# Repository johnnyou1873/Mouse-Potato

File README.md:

# Mouse-Potato
Micromouse design for AAMC 2024

## Major Components

### Microcontroller
STMicroelectronics STM32F411RETx

### Motors
*2x* CHF-GW12T-N20VA ABHL DC Worm Gear Motor
- Ratio: 42-A
- Voltage: 6V B45
- https://www.aliexpress.us/item/3256801422029348.html
- Requires shortening of the encoder board and resoldering of the cables

### Motor Driver
STMicroelectronics L293DD

### IMU
TDK InvenSense ICM-42688-P

### ToF Sensors
*3x* Adafruit VL6180X Time of Flight Micro-LIDAR Distance Sensor Breakout

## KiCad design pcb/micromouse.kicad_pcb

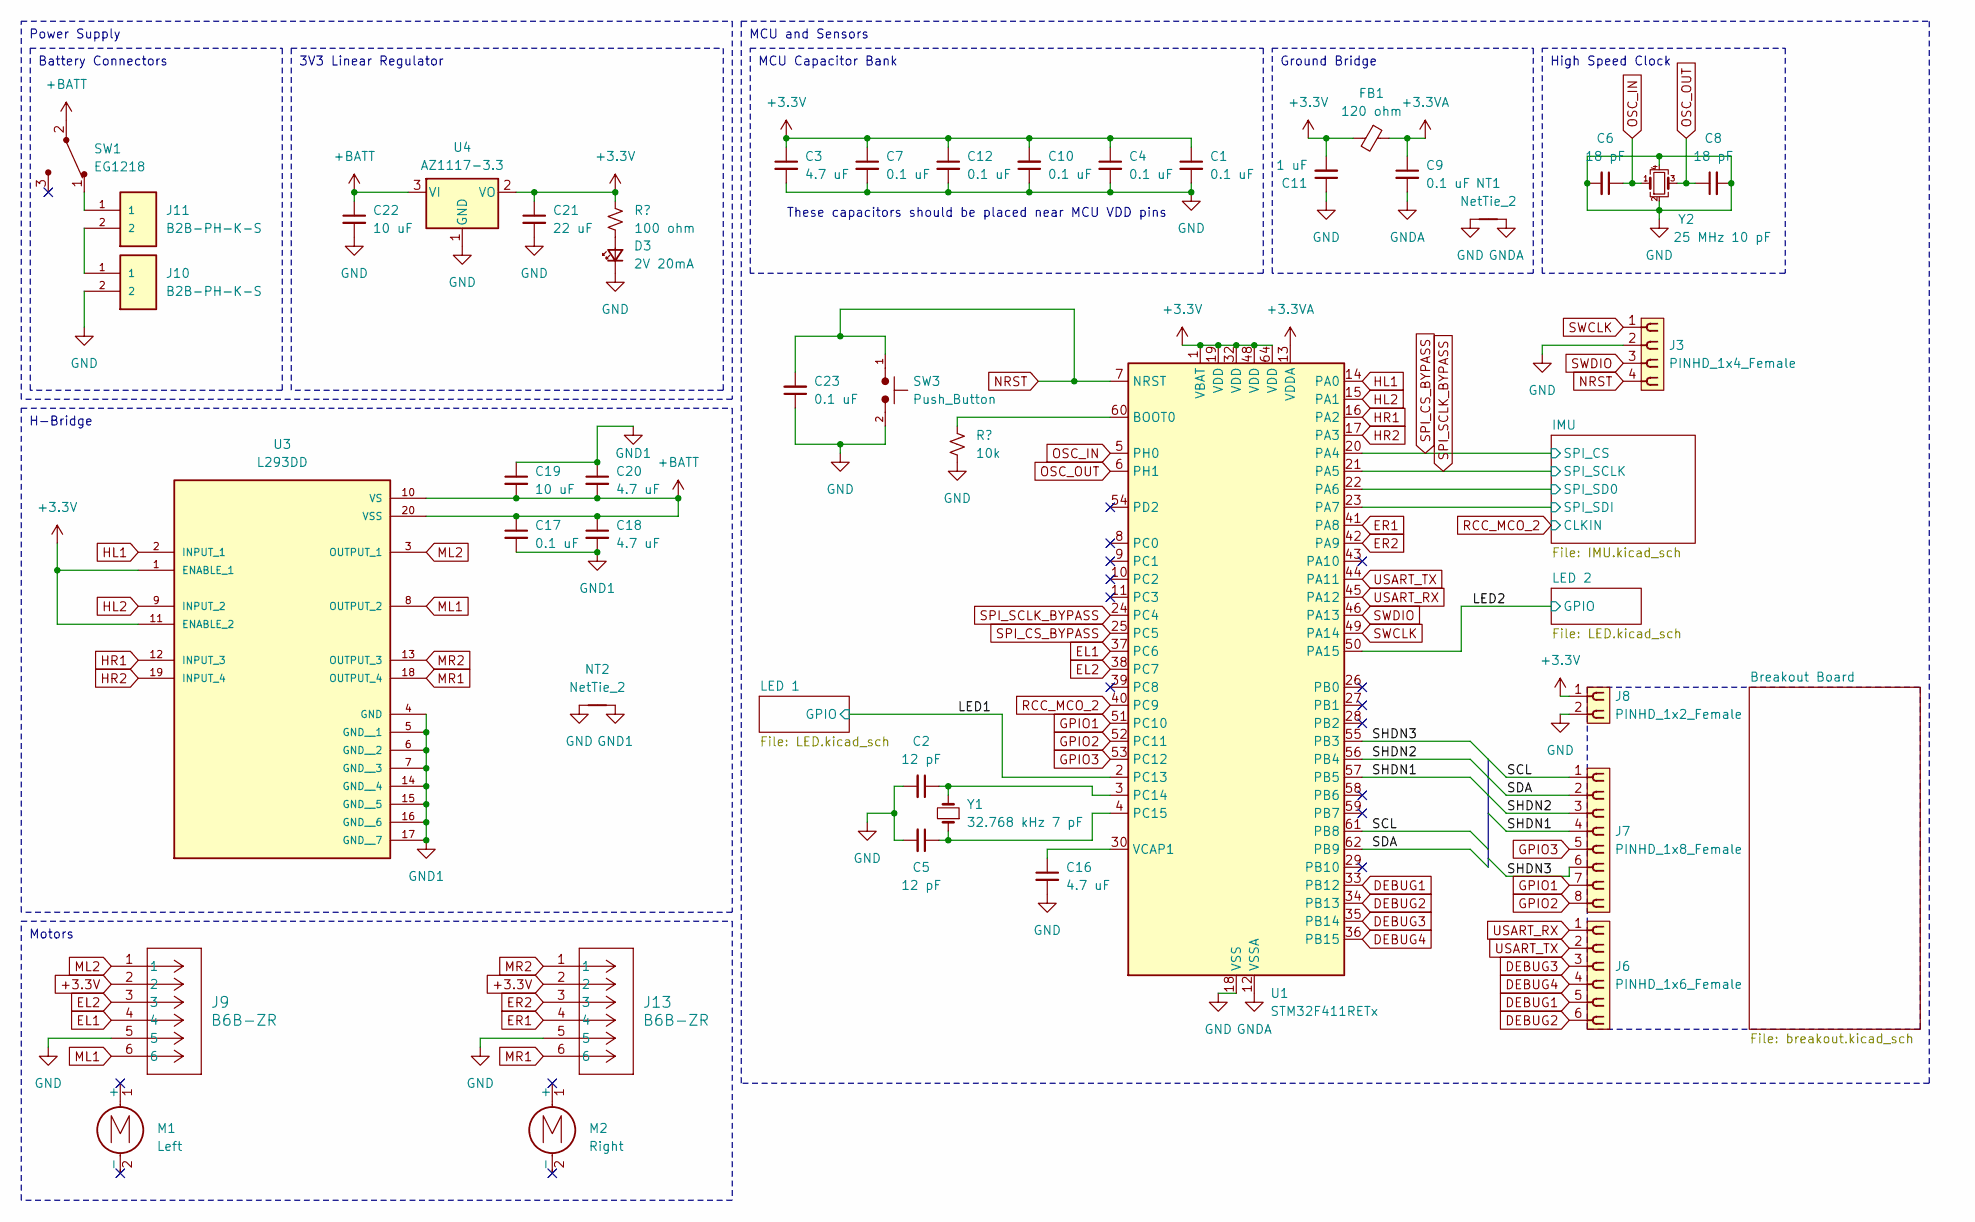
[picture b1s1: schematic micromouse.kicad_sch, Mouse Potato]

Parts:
C1, C4, C7, C9, C10, C12, C17, C23: 0.1 uF; C_0603_1608Metric
C2, C5: 12 pF; C_0603_1608Metric
C3, C16, C18, C20: 4.7 uF; C_0603_1608Metric
C6, C8: 18 pF; C_0603_1608Metric
C11: 1 uF; C_0603_1608Metric
C19, C22: 10 uF; C_0603_1608Metric
C21: 22 uF; C_0603_1608Metric
D3: 2V 20mA; LED_0603_1608Metric
FB1: 120 ohm; L_0603_1608Metric
J3: PINHD_1x4_Female; PinSocket_1x04_P2.54mm_Vertical
J6: PINHD_1x6_Female; PinSocket_2x03_P2.54mm_Vertical
J7: PINHD_1x8_Female; PinSocket_2x04_P2.54mm_Vertical
J8: PINHD_1x2_Female; PinSocket_1x02_P2.54mm_Vertical
J9, J13: B6B-ZR; CONN_B6B-ZR_JST
J10, J11: B2B-PH-K-S; JST_B2B-PH-K-S_LF__SN_; PARTREV N/A; DIGI-KEY_PART_NUMBER 455-1704-ND
M1: Left; MM_Motor_Left
M2: Right; MM_Motor_Right
NT1, NT2: NetTie_2; NetTie-2_SMD_Pad0.5mm
R2: 10k; R_0603_1608Metric
R5: 100 ohm; R_0603_1608Metric
SW1: EG1218; Switch_Slide_11.6x4mm_EG1218; MPN EG1218; Digi-Key_PN EG1903-ND
SW3: Push_Button; SolderJumper-2_P1.3mm_Open_Pad1.0x1.5mm
U1: STM32F411RETx; LQFP-64_10x10mm_P0.5mm
U3: L293DD; SOIC127P1032X265-20N; PARTREV N/A
U4: AZ1117-3.3; SOT-223-3_TabPin2
Y1: 32.768 kHz 7 pF; XTAL_SC32S-7PF20PPM_EPS
Y2: 25 MHz 10 pF; XTAL4P_RH100-25.000-10-F-3030-EXT-TR_RAL

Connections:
+3.3V: C1.1, C3.1, C4.1, C7.1, C10.2, C11.2, C12.1, C21.1, FB1.2, J8.1, J9.2, J13.2, R5.2, U1.1 (VBAT), U1.19 (VDD), U1.32 (VDD), U1.48 (VDD), U1.64 (VDD), U3.1 (ENABLE_1), U3.11 (ENABLE_2), U4.2 (VO); also elsewhere on the board
+3.3VA: C9.1, FB1.1, U1.13 (VDDA)
+BATT: C17.1, C18.1, C19.2, C20.2, C22.1, SW1.2, U3.10 (VS), U3.20 (VSS), U4.3 (VI)
/IMU/SPI_SD0: U1.22 (PA6); also elsewhere on the board
/IMU/SPI_SDI: U1.23 (PA7); also elsewhere on the board
/LED1: U1.2 (PC13); also elsewhere on the board
/LED2: U1.50 (PA15); also elsewhere on the board
/SCL: J7.1, U1.61 (PB8)
/SDA: J7.2, U1.62 (PB9)
/SHDN1: J7.4, U1.57 (PB5)
/SHDN2: J7.3, U1.56 (PB4)
/SHDN3: J7.6, U1.55 (PB3)
DEBUG1: J6.5, U1.33 (PB12)
DEBUG2: J6.6, U1.34 (PB13)
DEBUG3: J6.3, U1.35 (PB14)
DEBUG4: J6.4, U1.36 (PB15)
EL1: J9.4, U1.37 (PC6)
EL2: J9.3, U1.38 (PC7)
ER1: J13.4, U1.41 (PA8)
ER2: J13.3, U1.42 (PA9)
GND1: C17.2, C18.2, C19.1, C20.1, NT2.2, U3.4 (GND), U3.5 (GND__1), U3.6 (GND__2), U3.7 (GND__3), U3.14 (GND__4), U3.15 (GND__5), U3.16 (GND__6), U3.17 (GND__7)
GNDA: C9.2, NT1.2, U1.12 (VSSA)
GPIO1: J7.7, U1.51 (PC10)
GPIO2: J7.8, U1.52 (PC11)
GPIO3: J7.5, U1.53 (PC12)
HL1: U1.14 (PA0), U3.2 (INPUT_1)
HL2: U1.15 (PA1), U3.9 (INPUT_2)
HR1: U1.16 (PA2), U3.12 (INPUT_3)
HR2: U1.17 (PA3), U3.19 (INPUT_4)
ML1: J9.6, U3.8 (OUTPUT_2)
ML2: J9.1, U3.3 (OUTPUT_1)
MR1: J13.6, U3.18 (OUTPUT_4)
MR2: J13.1, U3.13 (OUTPUT_3)
NRST: C23.2, J3.4, SW3.1, U1.7 (NRST)
unnamed: D3.2 (A), R5.1
unnamed: J10.1, J11.2
unnamed: J11.1, SW1.1
unnamed: C2.1, U1.3 (PC14), Y1.2
unnamed: C5.1, U1.4 (PC15), Y1.1
unnamed: C16.1, U1.30 (VCAP1)
OSC_IN: C6.1, U1.5 (PH0), Y2.1
OSC_OUT: C8.1, U1.6 (PH1), Y2.3
RCC_MCO_2: U1.40 (PC9); also elsewhere on the board
SPI_CS_BYPASS: U1.20 (PA4), U1.25 (PC5); also elsewhere on the board
SPI_SCLK_BYPASS: U1.21 (PA5), U1.24 (PC4); also elsewhere on the board
SWCLK: J3.1, U1.49 (PA14)
SWDIO: J3.3, U1.46 (PA13)
USART_RX: J6.1, U1.45 (PA12)
USART_TX: J6.2, U1.44 (PA11)

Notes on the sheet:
H-Bridge
3V3 Linear Regulator
Ground Bridge
MCU and Sensors
Motors
MCU Capacitor Bank
Power Supply
High Speed Clock
Battery Connectors
These capacitors should be placed near MCU VDD pins

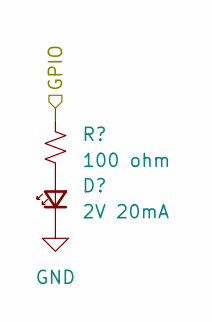
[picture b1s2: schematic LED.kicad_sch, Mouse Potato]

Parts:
D1: 2V 20mA; LED_0603_1608Metric
R1: 100 ohm; R_0603_1608Metric

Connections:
/LED1: R1.2; also elsewhere on the board
unnamed: D1.2 (A), R1.1

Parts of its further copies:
D2: 2V 20mA; LED_0603_1608Metric
R3: 100 ohm; R_0603_1608Metric

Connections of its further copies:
/LED2: R3.2; also elsewhere on the board
unnamed: D2.2 (A), R3.1

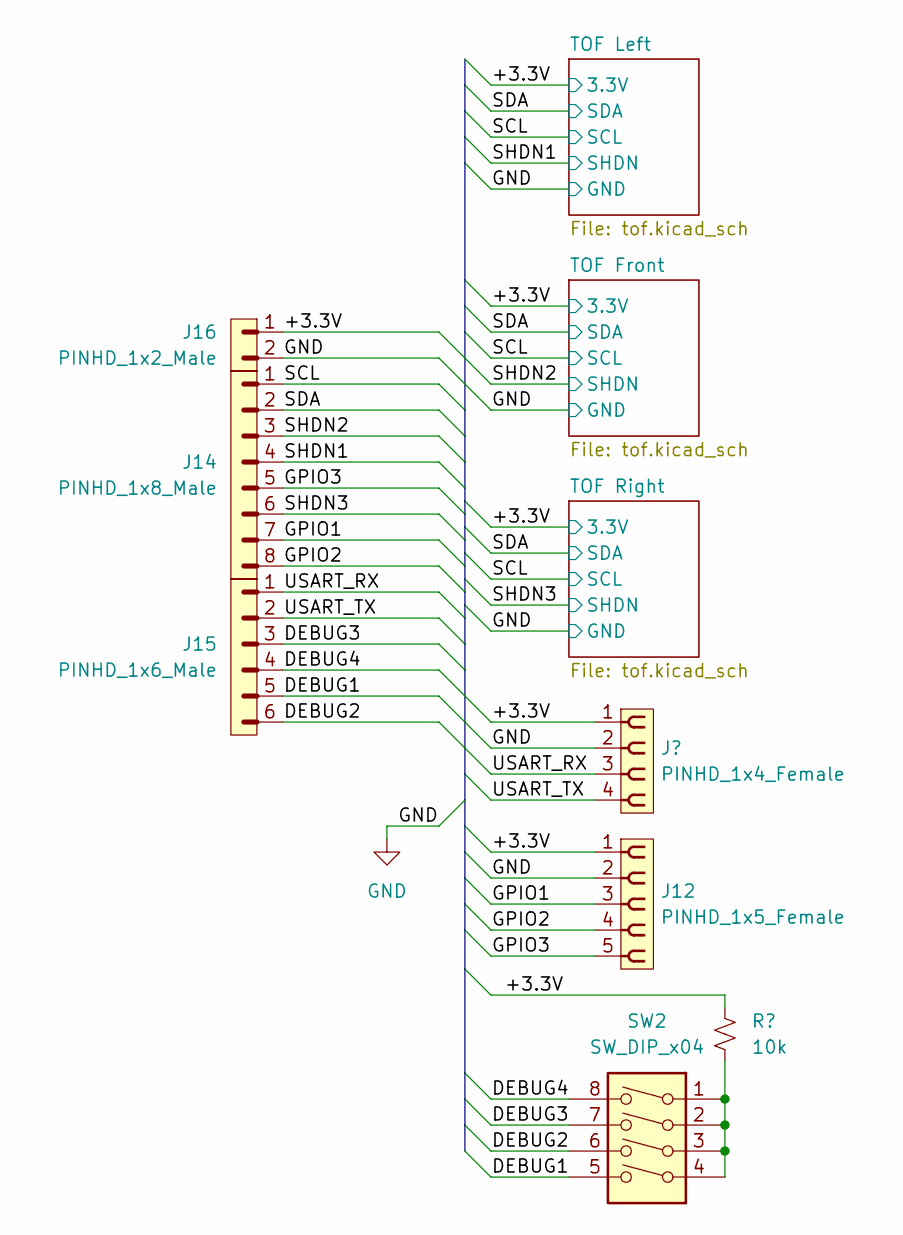
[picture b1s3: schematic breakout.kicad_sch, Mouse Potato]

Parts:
J5: PINHD_1x4_Female; PinSocket_1x04_P2.54mm_Vertical
J12: PINHD_1x5_Female; PinSocket_1x05_P2.54mm_Vertical
J14: PINHD_1x8_Male; PinHeader_2x04_P2.54mm_Vertical
J15: PINHD_1x6_Male; PinHeader_2x03_P2.54mm_Vertical
J16: PINHD_1x2_Male; PinHeader_1x02_P2.54mm_Vertical
R2: 10k; R_0603_1608Metric
SW2: SW_DIP_x04; 218-4LPST

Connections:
/Breakout Board/DEBUG1: J15.5, SW2.5
/Breakout Board/DEBUG2: J15.6, SW2.6
/Breakout Board/DEBUG3: J15.3, SW2.7
/Breakout Board/DEBUG4: J15.4, SW2.8
/Breakout Board/GPIO1: J12.3, J14.7
/Breakout Board/GPIO2: J12.4, J14.8
/Breakout Board/GPIO3: J12.5, J14.5
/Breakout Board/SCL: J14.1; also elsewhere on the board
/Breakout Board/SDA: J14.2; also elsewhere on the board
/Breakout Board/SHDN1: J14.4; also elsewhere on the board
/Breakout Board/SHDN2: J14.3; also elsewhere on the board
/Breakout Board/SHDN3: J14.6; also elsewhere on the board
/Breakout Board/USART_RX: J5.3, J15.1
/Breakout Board/USART_TX: J5.4, J15.2

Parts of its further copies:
R6: 10k; R_0603_1608Metric

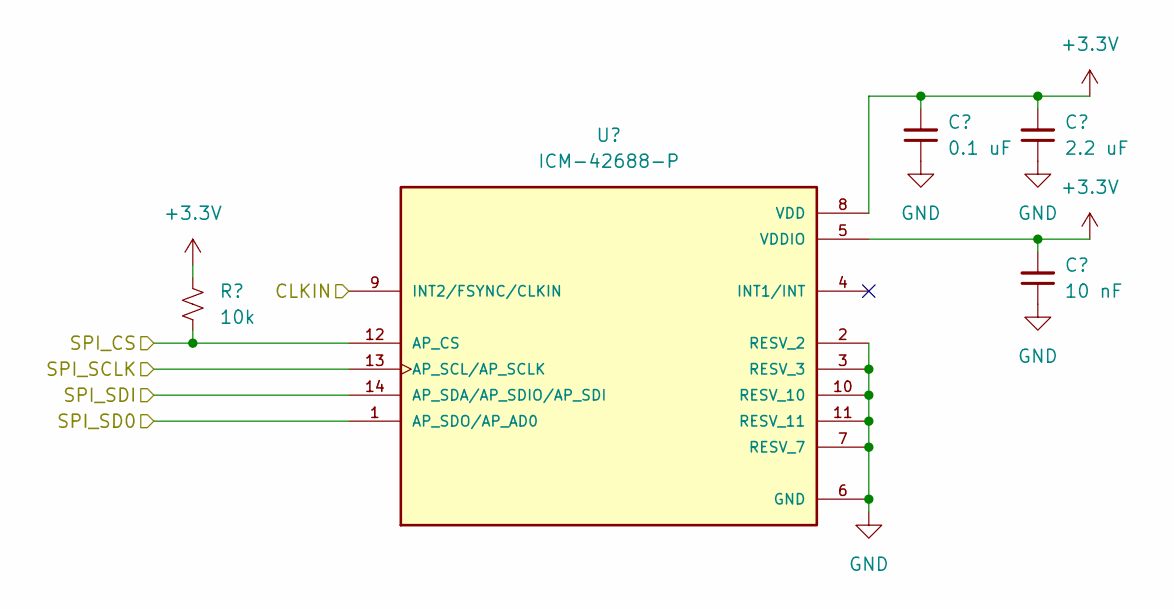
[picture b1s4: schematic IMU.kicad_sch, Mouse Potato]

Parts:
C13: 10 nF; C_0603_1608Metric
C14: 0.1 uF; C_0603_1608Metric
C15: 2.2 uF; C_0603_1608Metric
R4: 10k; R_0603_1608Metric
U2: ICM-42688-P; PQFN50P300X250X97-14N; PARTREV 1.2

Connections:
+3.3V: C13.2, C14.2, C15.2, R4.2, U2.5 (VDDIO), U2.8 (VDD); also elsewhere on the board
/IMU/SPI_SD0: U2.1 (AP_SDO/AP_AD0); also elsewhere on the board
/IMU/SPI_SDI: U2.14 (AP_SDA/AP_SDIO/AP_SDI); also elsewhere on the board
RCC_MCO_2: U2.9 (INT2/FSYNC/CLKIN); also elsewhere on the board
SPI_CS_BYPASS: R4.1, U2.12 (AP_CS); also elsewhere on the board
SPI_SCLK_BYPASS: U2.13 (AP_SCL/AP_SCLK); also elsewhere on the board

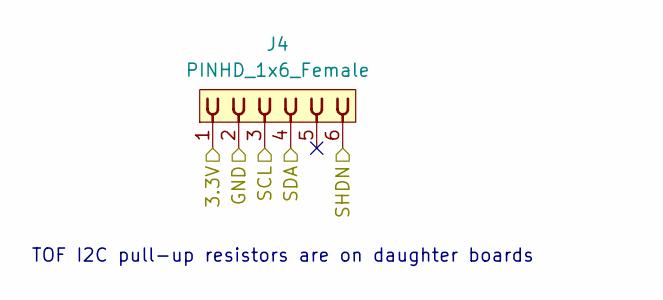
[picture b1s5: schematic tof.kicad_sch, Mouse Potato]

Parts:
J4: PINHD_1x6_Female; PinSocket_1x06_P2.54mm_Vertical

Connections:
/Breakout Board/SCL: J4.3; also elsewhere on the board
/Breakout Board/SDA: J4.4; also elsewhere on the board
/Breakout Board/SHDN3: J4.6; also elsewhere on the board

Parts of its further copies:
J1, J2: PINHD_1x6_Female; PinSocket_1x06_P2.54mm_Vertical

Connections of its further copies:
/Breakout Board/SCL: J1.3, J2.3; also elsewhere on the board
/Breakout Board/SDA: J1.4, J2.4; also elsewhere on the board
/Breakout Board/SHDN1: J1.6; also elsewhere on the board
/Breakout Board/SHDN2: J2.6; also elsewhere on the board

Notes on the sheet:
TOF I2C pull-up resistors are on daughter boards

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
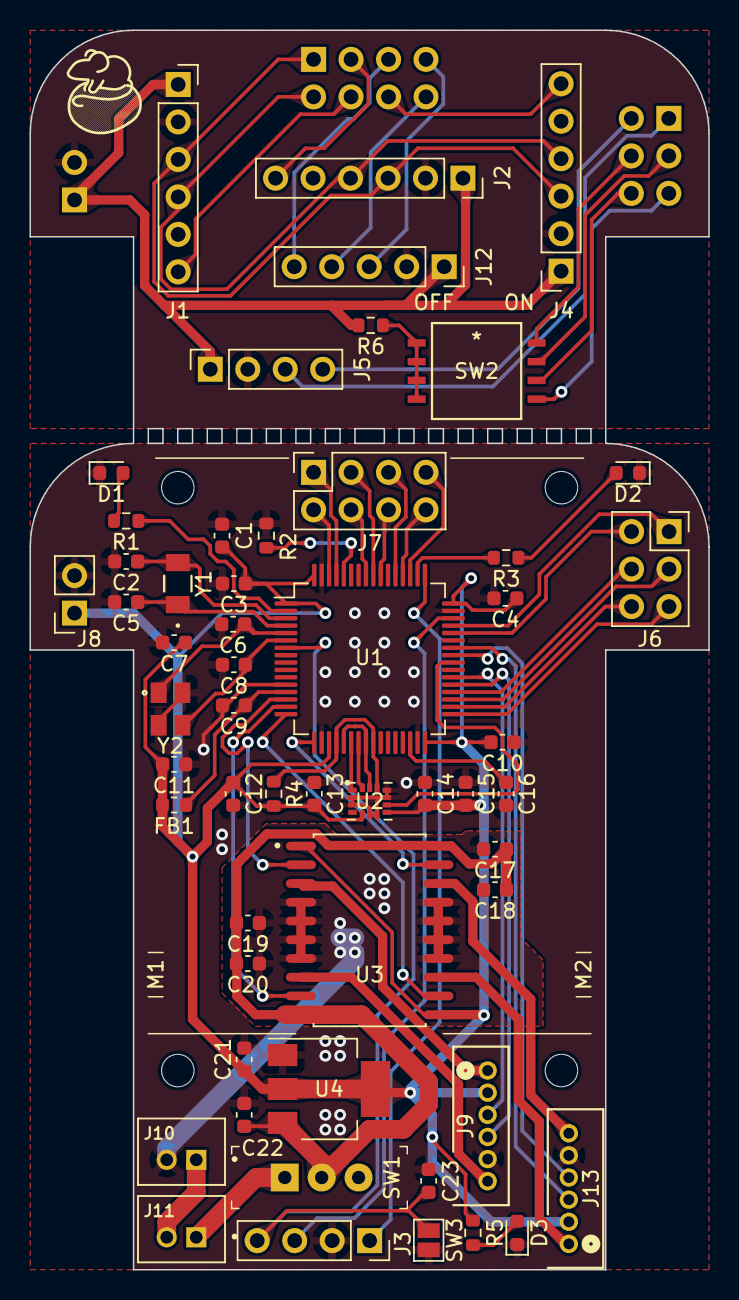
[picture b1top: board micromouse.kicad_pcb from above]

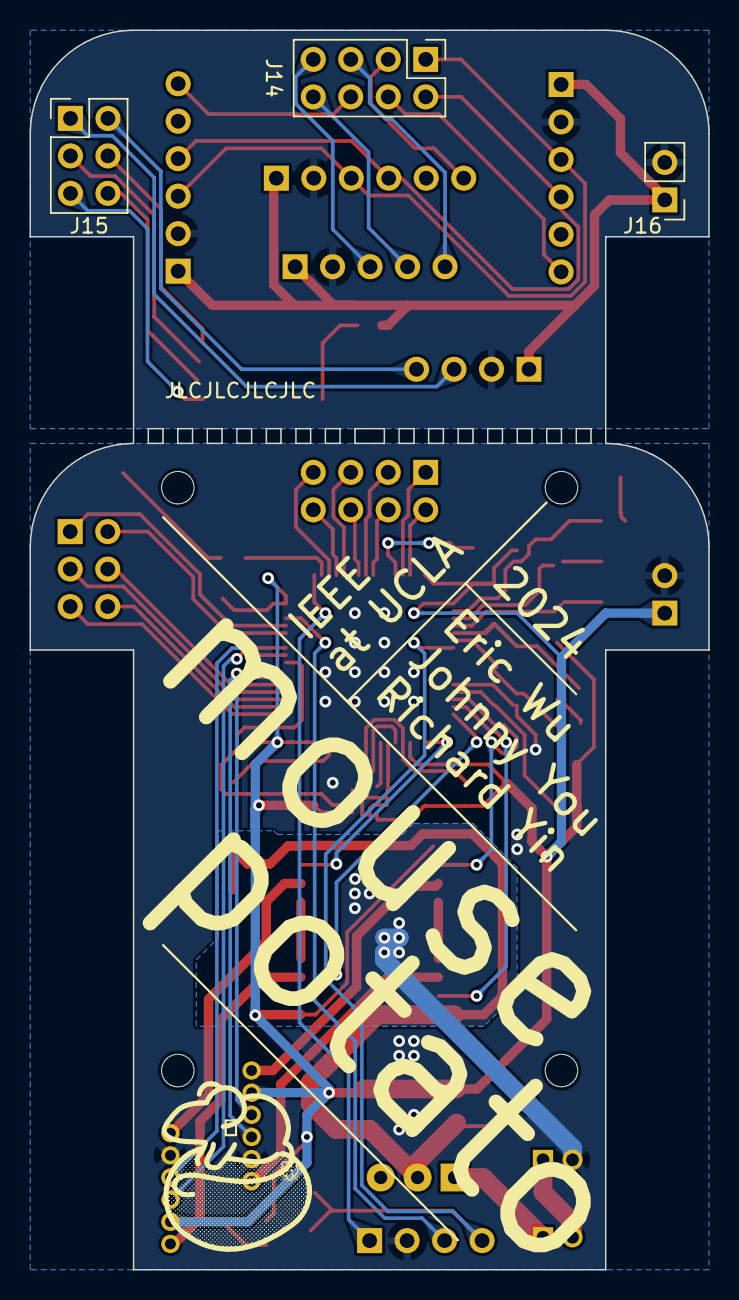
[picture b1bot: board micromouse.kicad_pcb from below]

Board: 2 copper layers, 46.0 x 84.0 mm, 62 parts (4 on the bottom side), 69 nets.

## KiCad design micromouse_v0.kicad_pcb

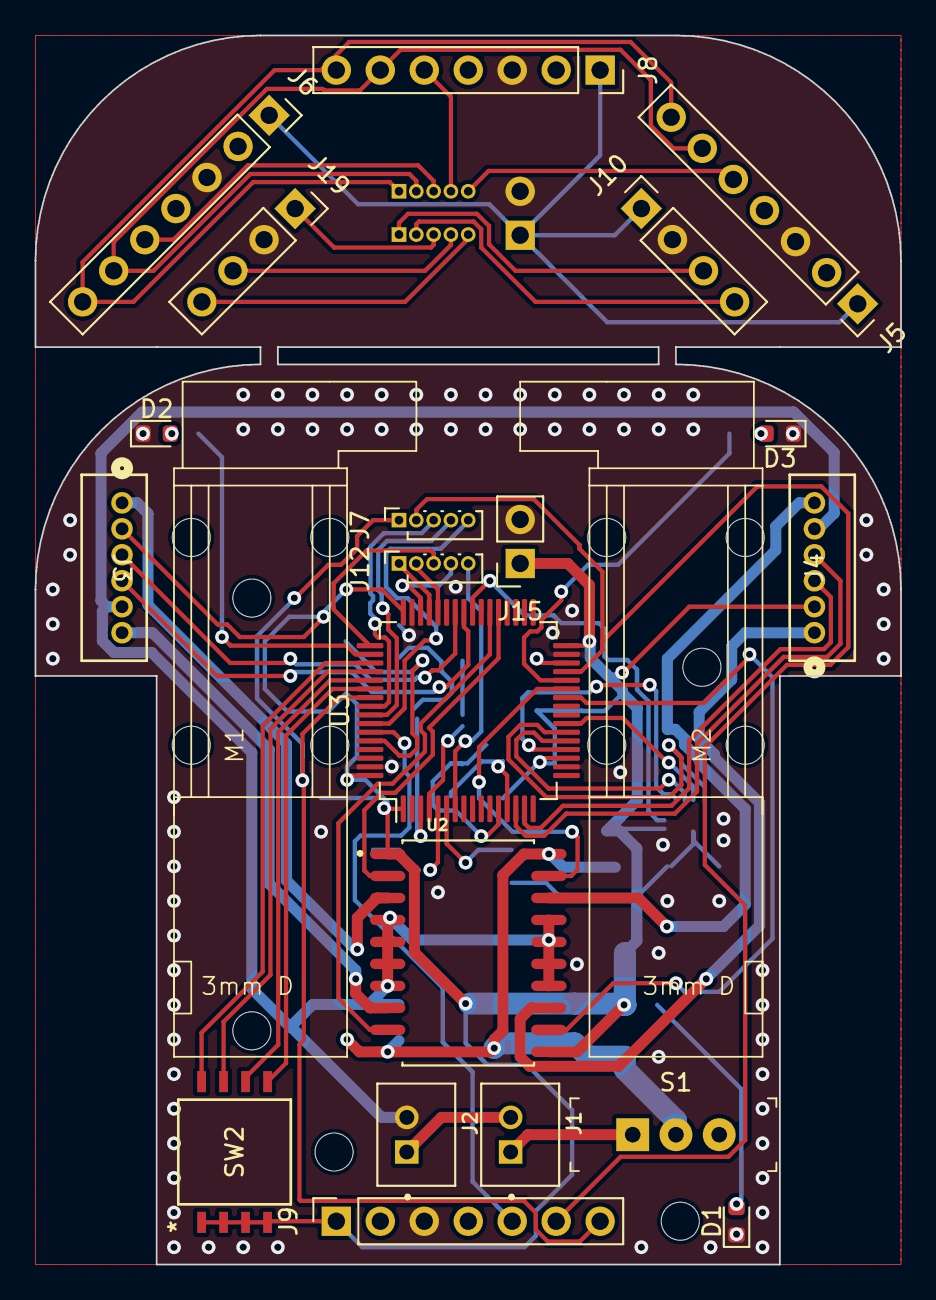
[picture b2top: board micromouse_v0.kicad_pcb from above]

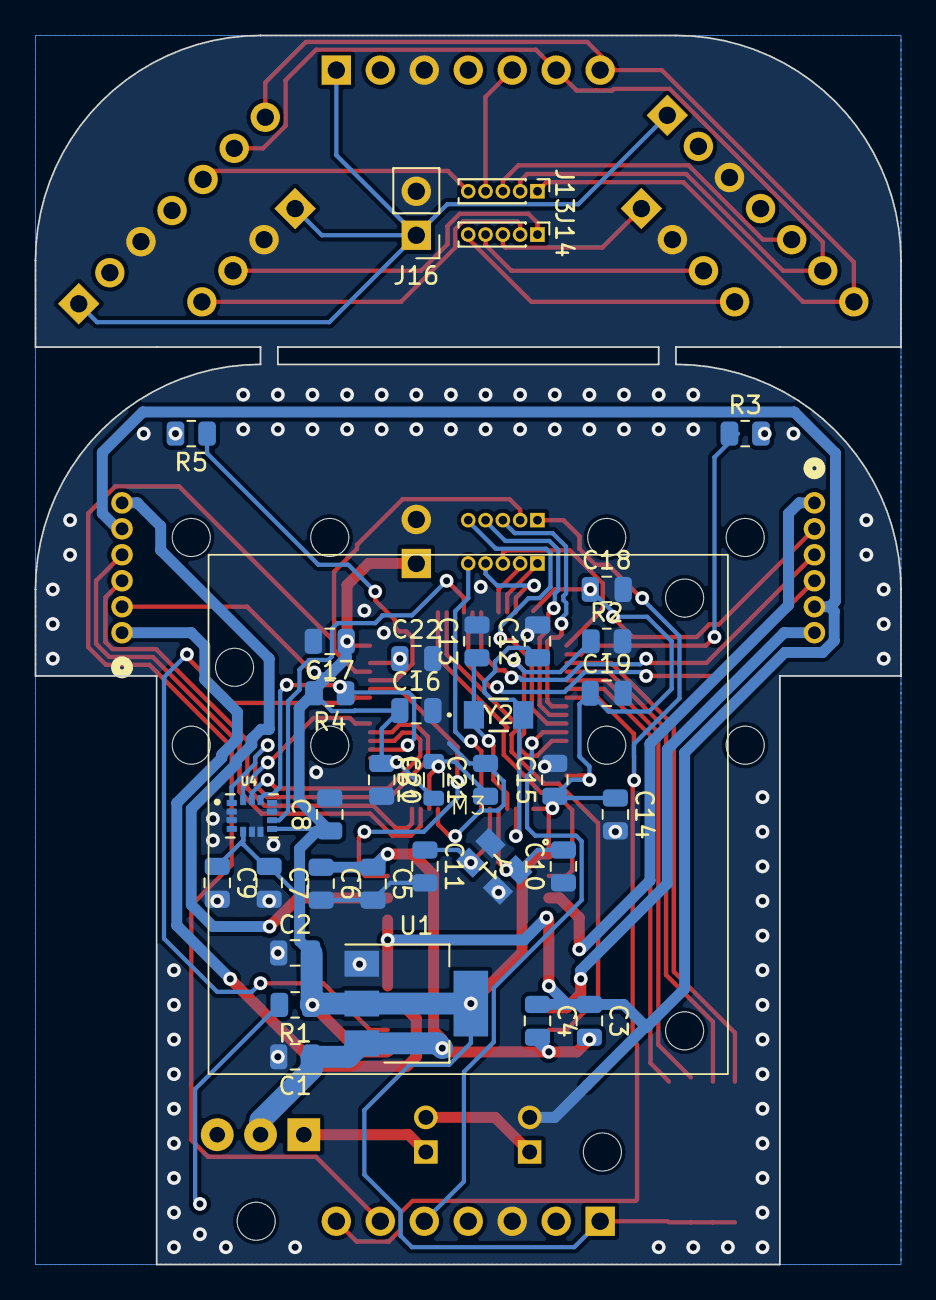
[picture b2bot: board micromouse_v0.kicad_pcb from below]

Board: 2 copper layers, 50.0 x 71.0 mm, 62 parts (38 on the bottom side), 62 nets.

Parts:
BT1, BT2: Battery_Cell; MountingHole_2.2mm_M2
C1, C3: 10 uF; C_0805_2012Metric
C2: 22 uF; C_0805_2012Metric
C4, C6, C14, C22: 4.7 uF; C_0805_2012Metric
C5, C7, C15, C16, C17, C18, C19, C21: 0.1 uF; C_0805_2012Metric
C8: 2.2 uF; C_0805_2012Metric
C9: 10 nF; C_0805_2012Metric
C10, C11: 18 pF; C_0805_2012Metric
C12, C13: 12 pF; C_0805_2012Metric
C20: 1 uF; C_0805_2012Metric
D1, D2, D3: 2V 20mA; LED_0603_1608Metric
FB1: 120 ohm; L_0805_2012Metric
J1, J2: B2B-PH-K-S; JST_B2B-PH-K-S_LF__SN_
J3, J4: B6B-ZR; CONN_B6B-ZR_JST
J5, J6, J8, J9: PINHD_1x7_Female; PinSocket_1x07_P2.54mm_Vertical
J7, J12: PINHD_1x5_Female; PinSocket_1x05_P1.00mm_Vertical
J10, J19: PINHD_1x4_Female; PinSocket_1x04_P2.54mm_Vertical
J13, J14: PINHD_1x5_Male; PinHeader_1x05_P1.00mm_Vertical
J15: PINHD_1x2_Female; PinSocket_1x02_P2.54mm_Vertical
J16: PINHD_1x2_Male; PinHeader_1x02_P2.54mm_Vertical
M1: Left; MM_Motor_Left
M2: Right; MM_Motor_Right
M3: KDB0305HA3-00C1J
NT1, NT2: NetTie_2; NetTie-2_SMD_Pad0.5mm
R1, R3, R5: 100 ohm; R_0805_2012Metric
R2, R4: 10k; R_0805_2012Metric
S1: EG1218; Switch_Slide_11.6x4mm_EG1218
SW2: SW_DIP_x04; 218-4LPST
U1: AZ1117-3.3; SOT-223-3_TabPin2
U2: L293DD; SOIC127P1032X265-20N
U3: STM32F411RETx; LQFP-64_10x10mm_P0.5mm
U4: ICM-42688-P; PQFN50P300X250X97-14N
Y1: 25 MHz 10 pF; XTAL4P_RH100-25.000-10-F-3030-EXT-TR_RAL
Y2: 32.768 kHz 7 pF; XTAL_SC32S-7PF20PPM_EPS

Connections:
+3.3V: C2.1, C7.1, C8.1, C9.1, C14.1, C15.1, C16.1, C17.1, C18.1, C19.1, C20.1, FB1.1, J3.2, J4.2, J9.1, J15.1, R1.1, R4.2, SW2.1, SW2.2, SW2.3, SW2.4, U1.2 (VO), U2.1 (ENABLE_1), U2.11 (ENABLE_2), U3.1 (VBAT), U3.19 (VDD), U3.32 (VDD), U3.48 (VDD), U3.64 (VDD), U4.5 (VDDIO), U4.8 (VDD)
+3.3VA: C21.1, FB1.2, U3.13 (VDDA)
+BATT: C1.1, C3.2, C4.2, C5.1, C6.1, S1.2, U1.3 (VI), U2.10 (VS), U2.20 (VSS)
/Breakout Board/+3.3V: J5.1, J6.1, J8.1, J10.1, J16.1
/Breakout Board/NRST: J14.5, J19.4
/Breakout Board/SCL: J5.6, J6.6, J8.6, J13.2
/Breakout Board/SDA: J5.7, J6.7, J8.7, J13.1
/Breakout Board/SHDN1: J6.5, J13.3
/Breakout Board/SHDN2: J8.5, J13.4
/Breakout Board/SHDN3: J5.5, J13.5
/Breakout Board/SWCLK: J14.3, J19.1
/Breakout Board/SWDIO: J14.4, J19.3
/Breakout Board/USART_RX: J10.3, J14.1
/Breakout Board/USART_TX: J10.4, J14.2
/IMU/SPI_CS: R4.1, U3.20 (PA4), U4.12 (AP_CS)
/IMU/SPI_SCLK: U3.21 (PA5), U4.13 (AP_SCL/AP_SCLK)
/IMU/SPI_SD0: U3.22 (PA6), U4.1 (AP_SDO/AP_AD0)
/IMU/SPI_SDI: U3.23 (PA7), U4.14 (AP_SDA/AP_SDIO/AP_SDI)
/LED1: R3.1, U3.50 (PA15)
/LED2: R5.1, U3.28 (PB2)
/SHDN1: J7.3, U3.56 (PB4)
/SHDN2: J7.4, U3.57 (PB5)
/SHDN3: J7.5, U3.58 (PB6)
/SHDN4: J9.5, U3.59 (PB7)
DEBUG1: SW2.8, U3.51 (PC10)
DEBUG2: SW2.7, U3.52 (PC11)
DEBUG3: SW2.6, U3.53 (PC12)
DEBUG4: SW2.5, U3.54 (PD2)
EL1: J3.4, U3.41 (PA8)
EL2: J3.3, U3.42 (PA9)
ER1: J4.4, U3.14 (PA0)
ER2: J4.3, U3.15 (PA1)
GND: C1.2, C2.2, C5.2, C6.2, C7.2, C8.2, C9.2, C10.1, C11.2, C12.2, C13.2, C14.2, C15.2, C16.2, C17.2, C18.2, C19.2, C20.2, C22.2, D1.1 (K), D2.1 (K), D3.1 (K), J2.2, J5.3, J6.3, J8.3, J9.3, J10.2, J15.2, J16.2, J19.2, NT1.1, NT2.1, R2.2, U1.1 (GND), U3.18 (VSS), U3.31 (VSS), U3.47 (VSS), U3.63 (VSS), U4.2 (RESV_2), U4.3 (RESV_3), U4.6 (GND), U4.7 (RESV_7), U4.10 (RESV_10), U4.11 (RESV_11), Y1.2, Y1.4
GND1: C3.1, C4.1, J3.5, J4.5, NT1.2, U2.4 (GND), U2.5 (GND__1), U2.6 (GND__2), U2.7 (GND__3), U2.14 (GND__4), U2.15 (GND__5), U2.16 (GND__6), U2.17 (GND__7)
GNDA: C21.2, NT2.2, U3.12 (VSSA)
HL1: U2.2 (INPUT_1), U3.37 (PC6)
HL2: U2.9 (INPUT_2), U3.38 (PC7)
HR1: U2.12 (INPUT_3), U3.26 (PB0)
HR2: U2.19 (INPUT_4), U3.27 (PB1)
I2C2_SCL: J7.2, J9.6, U3.29 (PB10)
I2C2_SDA: J7.1, J9.7, U3.55 (PB3)
ML1: J3.6, U2.8 (OUTPUT_2)
ML2: J3.1, U2.3 (OUTPUT_1)
MR1: J4.6, U2.18 (OUTPUT_4)
MR2: J4.1, U2.13 (OUTPUT_3)
NRST: J12.5, U3.7 (NRST)
unnamed: D1.2 (A), R1.2
unnamed: D2.2 (A), R3.2
unnamed: D3.2 (A), R5.2
unnamed: J1.1, S1.1
unnamed: J1.2, J2.1
unnamed: R2.1, U3.60 (BOOT0)
unnamed: C12.1, U3.3 (PC14), Y2.2
unnamed: C13.1, U3.4 (PC15), Y2.1
unnamed: C22.1, U3.30 (VCAP1)
OSC_IN: C10.2, U3.5 (PH0), Y1.1
OSC_OUT: C11.1, U3.6 (PH1), Y1.3
RCC_MCO_2: U3.40 (PC9), U4.9 (INT2/FSYNC/CLKIN)
SWCLK: J12.3, U3.49 (PA14)
SWDIO: J12.4, U3.46 (PA13)
USART_RX: J12.1, U3.45 (PA12)
USART_TX: J12.2, U3.44 (PA11)

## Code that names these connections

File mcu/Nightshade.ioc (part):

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Mcu.Name=STM32F411R(C-E)Tx
Mcu.Package=LQFP64
Mcu.UserName=STM32F411RETx
PA0-WKUP.Signal=S_TIM5_CH1
PA1.Signal=S_TIM5_CH2
PA10.Signal=GPIO_Output
PA11.Mode=Asynchronous
PA11.Signal=USART6_TX
PA12.Mode=Asynchronous
PA12.Signal=USART6_RX
PA13.Mode=Serial_Wire
PA13.Signal=SYS_JTMS-SWDIO
PA14.Mode=Serial_Wire
PA14.Signal=SYS_JTCK-SWCLK
PA2.Signal=S_TIM5_CH3
PA3.Signal=S_TIM5_CH4
PA4.Mode=NSS_Signal_Hard_Output
PA4.Signal=SPI1_NSS
PA5.Mode=Full_Duplex_Master
PA5.Signal=SPI1_SCK
PA6.Mode=Full_Duplex_Master
PA6.Signal=SPI1_MISO
PA7.Mode=Full_Duplex_Master
PA7.Signal=SPI1_MOSI
PA8.Signal=S_TIM1_CH1
PA9.Signal=S_TIM1_CH2
PB10.Signal=GPIO_Output
PB12.Signal=GPIO_Input
PB13.Signal=GPIO_Input
PB14.Signal=GPIO_Input
PB15.Signal=GPIO_Input
PB3.Signal=GPIO_Output
PB4.Signal=GPIO_Output
PB5.GPIOParameters=PinState,GPIO_PuPd,GPIO_ModeDefaultOutputPP
PB5.GPIO_ModeDefaultOutputPP=GPIO_MODE_OUTPUT_OD
PB5.GPIO_PuPd=GPIO_NOPULL
PB5.PinState=GPIO_PIN_SET
PB5.Signal=GPIO_Output
PB8.Mode=I2C
PB8.Signal=I2C1_SCL
PB9.Mode=I2C
PB9.Signal=I2C1_SDA
PC10.Mode=Full_Duplex_Master
PC10.Signal=SPI3_SCK
PC11.Mode=Full_Duplex_Master
PC11.Signal=SPI3_MISO
PC12.Mode=Full_Duplex_Master
PC12.Signal=SPI3_MOSI
PC13-ANTI_TAMP.Signal=GPIO_Output
PC14-OSC32_IN.Mode=LSE-External-Oscillator
PC14-OSC32_IN.Signal=RCC_OSC32_IN
PC15-OSC32_OUT.Mode=LSE-External-Oscillator
PC15-OSC32_OUT.Signal=RCC_OSC32_OUT
PC6.Signal=S_TIM3_CH1
PC7.Signal=S_TIM3_CH2
PC9.Mode=Clock-out-2
PC9.Signal=RCC_MCO_2
PH0\ -\ OSC_IN.Mode=HSE-External-Oscillator
PH0\ -\ OSC_IN.Signal=RCC_OSC_IN
PH1\ -\ OSC_OUT.Mode=HSE-External-Oscillator
PH1\ -\ OSC_OUT.Signal=RCC_OSC_OUT
RCC.HSE_VALUE=25000000
RCC.SYSCLKFreq_VALUE=16000000
board=custom

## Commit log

2023-12-24 Create pcb
2024-01-17 Fixed folder structure
2024-01-19 added MCU programming
2024-01-19 fixed mcu
2024-01-19 fixed gitignore
2024-01-19 added "switch" (jumper)
2024-02-01 added reset jumper to PCB
2024-02-01 update board art (still need to put pictures, though)
2024-02-02 added board art
2024-02-02 regenerated schematic pdf
2024-02-02 Added gerbers and drill files
2024-02-02 reformatted gerbers
2024-02-04 Updated board from MM lead feedback
2024-02-04 Updated gerbers
2024-02-04 Fixed mousebites
2024-02-06 Fixed PCB silkscreen, teardrops
2024-02-08 Regenerate Gerbers
2024-02-21 Removed redundant trace segment
2024-02-27 Add manufacturer specs
